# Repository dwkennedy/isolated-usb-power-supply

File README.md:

# isolated-usb-power-supply

BOM

Quanity, Description, Part Number
- 1, Recom RP15-1205SA  9-18V to 5V dc/dc isolated power supply, P/N 919-RP15-1205SA Mouser
- 2, SMD MLCC CAPACITOR CER 10UF 25V size 1812, P/N 445-7908-1-ND DigiKey
- 2, SMD MLCC CAPACITOR CER 470PF 2KV size 1808, P/N 445-11906-1-ND DigiKey
- 1, SMD FUSE BOARD MOUNT 1.6A 32VDC size 0603, P/N SF-0603SP160-2CT-ND DigiKey
- 1, SMD CMC 160UH 2.3A 2LN (common mode choke), P/N 283-4436-1-ND DigiKey
- 2, CONN PCB USB RA FEM TYPE A SMD, P/N AE11187-ND DigiKey
- 2, powerpole right angle contact horizontal (bottom) P/N 1336G1
- 1, powerpole PP15/45 housing, black P/N 1327
- 1, powerpole PP15/45 housing, red P/N 1327
- 4, #3 pan head screws, 5/8" long

FILES

- usb_power.brd    EAGLE board layout
- usb_power.sch    EAGLE schematic
- enclosure.SLDPRT Solidworks part, enclosure body
- enclosure.STL    enclosure rendered in STL for printing
- cover.SLDPRT     cover of enclosure
- cover.STL        cover rendered in STL for printing

Requires Doug's EAGLE library https://github.com/dwkennedy/eagle-library

TODO

Notes from first spin of PCB: pads for SMD fuse are too widely spaced for 0603 part.  SMD fuse should be changed to another part, because 0603 is difficult to hand solder. Also, holes and pads for RECOM RP-15-1205SA are too small after plating.  The USB part footprint doesn't have exposed copper to solder the tabs that go through the board. Hot glue fixes the wobbly USB connectors :)  Might consider moving USB connectors a little farther from the RP15-1205SA can in case they need to be resoldered at some point.

Improvements: add biasing resistors to 5VDC output to enable higher current on devices that support that charging protocol.  Identify a isolated DC/DC module that is less expensive and/or higher current than the RP15-1205SA.

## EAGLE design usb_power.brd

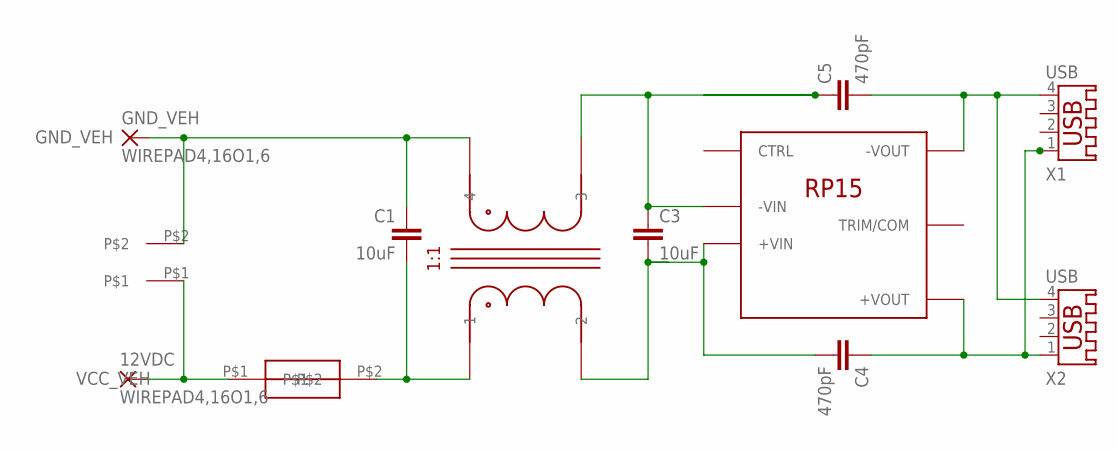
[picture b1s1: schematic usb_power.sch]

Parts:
12VDC: WIREPAD4,16O1,6; 4,16O1,6
C1, C3: 10uF; C1812
C4, C5: 470pF; C1808
GND_VEH: WIREPAD4,16O1,6; 4,16O1,6
RECOM: RP15-1205SA; RP15
U$2: 1.6A; C1608
U$3: COMMON-MODE-CHOKE; CMS2
U$4: POWERPOLE_RIGHT; 1336G1
X1, X2: USB; USB-A003

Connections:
GND_VEH: C1.1, GND_VEH.1, U$3.4, U$4.P$2
unnamed: C1.2, U$2.P$2, U$3.1
unnamed: C3.1, C5.1, RECOM.-VIN, U$3.3
unnamed: C3.2, C4.2, RECOM.+VIN, U$3.2
unnamed: C5.2, RECOM.-VOUT, X1.4, X2.4
VCC_ISO: C4.1, RECOM.+VOUT, X1.1, X2.1
VCC_VEH: 12VDC.1, U$2.P$1, U$4.P$1

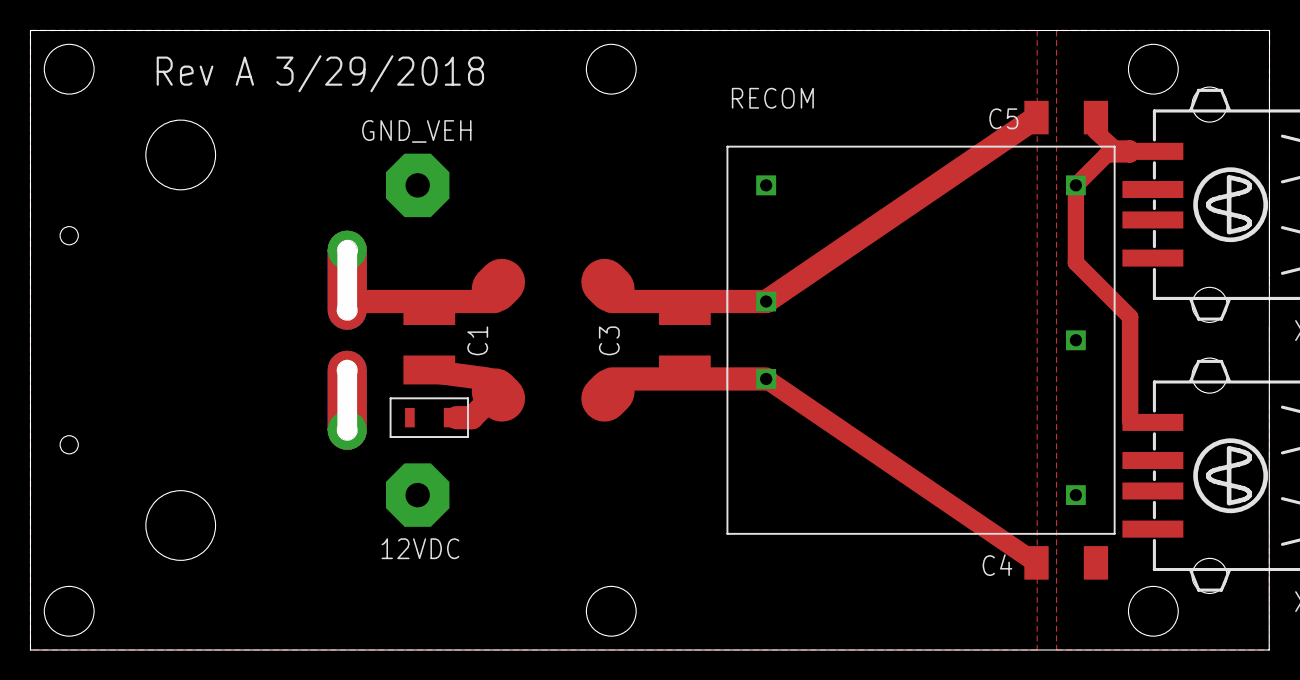
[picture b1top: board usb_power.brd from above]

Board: 2 copper layers, 80.0 x 39.3 mm, 12 parts (0 on the bottom side), 7 nets.
